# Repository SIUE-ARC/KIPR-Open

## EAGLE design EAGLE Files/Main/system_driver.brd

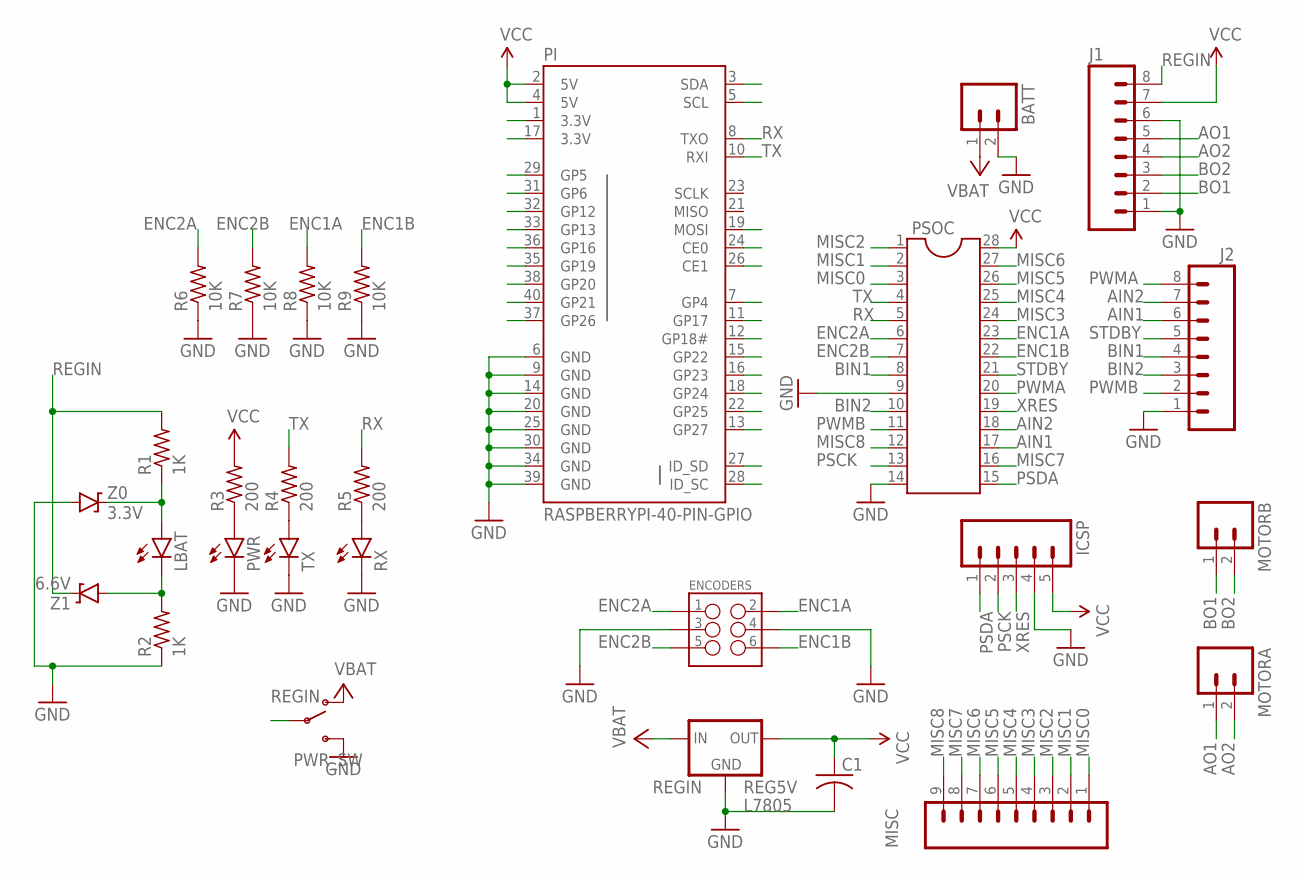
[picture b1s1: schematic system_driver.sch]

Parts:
BATT: M023.5MM; SCREWTERMINAL-3.5MM-2
C1: C-US025-024X044; C025-024X044
ENCODERS: M03X2FEMALE; 2X3
ICSP: M05LOCK_LONGPADS; 1X05_LOCK_LONGPADS
J1, J2: M08LONGPADS; 1X08_LONGPADS
LBAT: LED-FKIT-1206; FKIT-LED-1206
MISC: M09LONGPADS; 1X09_LONGPADS
MOTORA: M023.5MM; SCREWTERMINAL-3.5MM-2
MOTORB: M023.5MM; SCREWTERMINAL-3.5MM-2
PI: RASPBERRYPI-40-PIN-GPIO; 2X20-SHROUDED
PSOC: DIL28-3
PWR: LED-FKIT-1206; FKIT-LED-1206
PWR_SW: SWITCH-SPDTPTH; SWITCH-SPDT
R1, R2: 1K; M1206
R3, R4, R5: 200; M1206
R6, R7, R8, R9: 10K; M1206
REG5V: L7805; 78XXL
RX: LED-FKIT-1206; FKIT-LED-1206
TX: LED-FKIT-1206; FKIT-LED-1206
Z0: 3.3V; SOD-123
Z1: 6.6V; SOD-123

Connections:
3.3V: PI.1 (3.3V), PI.17 (3.3V)
AIN1: J2.6, PSOC.17
AIN2: J2.7, PSOC.18
AO1: J1.5, MOTORA.1
AO2: J1.4, MOTORA.2
BIN1: J2.4, PSOC.8
BIN2: J2.3, PSOC.10
BO1: J1.2, MOTORB.1
BO2: J1.3, MOTORB.2
CE0: PI.24 (CE0)
CE1: PI.26 (CE1)
ENC1A: ENCODERS.2, PSOC.23, R8.2
ENC1B: ENCODERS.6, PSOC.22, R9.2
ENC2A: ENCODERS.1, PSOC.6, R6.2
ENC2B: ENCODERS.5, PSOC.7, R7.2
GND: BATT.2, C1.2, ENCODERS.3, ENCODERS.4, ICSP.4, J1.1, J1.6, J2.1, PI.6 (GND), PI.9 (GND), PI.14 (GND), PI.20 (GND), PI.25 (GND), PI.30 (GND), PI.34 (GND), PI.39 (GND), PSOC.9, PSOC.14, PWR.C, PWR_SW.3 (S), R2.1, R6.1, R7.1, R8.1, R9.1, REG5V.IN (GND), RX.C, TX.C, Z0.A
GP4: PI.7 (GP4)
GP5: PI.29 (GP5)
GP6: PI.31 (GP6)
GP12: PI.32 (GP12)
GP13: PI.33 (GP13)
GP16: PI.36 (GP16)
GP17: PI.11 (GP17)
GP18: PI.12 (GP18#)
GP19: PI.35 (GP19)
GP20: PI.38 (GP20)
GP21: PI.40 (GP21)
GP22: PI.15 (GP22)
GP23: PI.16 (GP23)
GP24: PI.18 (GP24)
GP25: PI.22 (GP25)
GP26: PI.37 (GP26)
GP27: PI.13 (GP27)
ID_SC: PI.28 (ID_SC)
ID_SD: PI.27 (ID_SD)
MISC0: MISC.1, PSOC.3
MISC1: MISC.2, PSOC.2
MISC2: MISC.3, PSOC.1
MISC3: MISC.4, PSOC.24
MISC4: MISC.5, PSOC.25
MISC5: MISC.6, PSOC.26
MISC6: MISC.7, PSOC.27
MISC7: MISC.8, PSOC.16
MISC8: MISC.9, PSOC.12
MOSI: PI.19 (MOSI)
unnamed: LBAT.A, R1.1, Z0.C
unnamed: LBAT.C, R2.2, Z1.A
unnamed: PWR.A, R3.1
unnamed: R4.1, TX.A
unnamed: R5.1, RX.A
PI_SCL: PI.5 (SCL)
PI_SDA: PI.3 (SDA)
PSCK: ICSP.2, PSOC.13
PSDA: ICSP.1, PSOC.15
PWMA: J2.8, PSOC.20
PWMB: J2.2, PSOC.11
REGIN: J1.8, PWR_SW.2, R1.2, REG5V.OUT (IN), Z1.C
RX: PI.8 (TXO), PSOC.5, R5.2
STDBY: J2.5, PSOC.21
TX: PI.10 (RXI), PSOC.4, R4.2
V+: BATT.1, PWR_SW.1 (O)
VCC: C1.1, ICSP.5, J1.7, PI.2 (5V), PI.4 (5V), PSOC.28, R3.2, REG5V.GND (OUT)
XRES: ICSP.3, PSOC.19

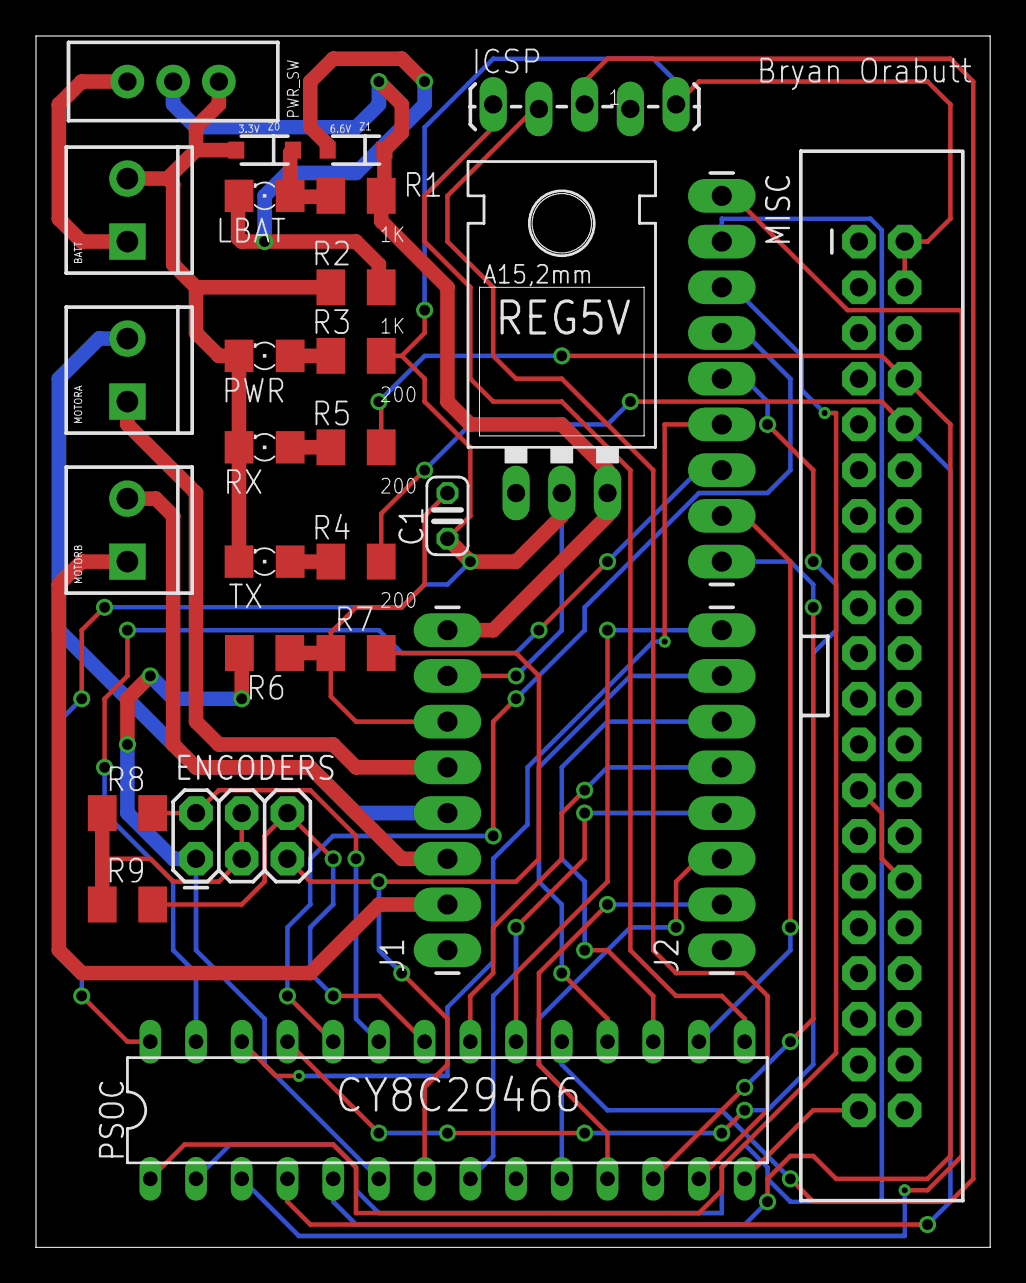
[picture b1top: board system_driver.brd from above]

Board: 2 copper layers, 53.0 x 67.3 mm, 28 parts (0 on the bottom side), 39 nets.

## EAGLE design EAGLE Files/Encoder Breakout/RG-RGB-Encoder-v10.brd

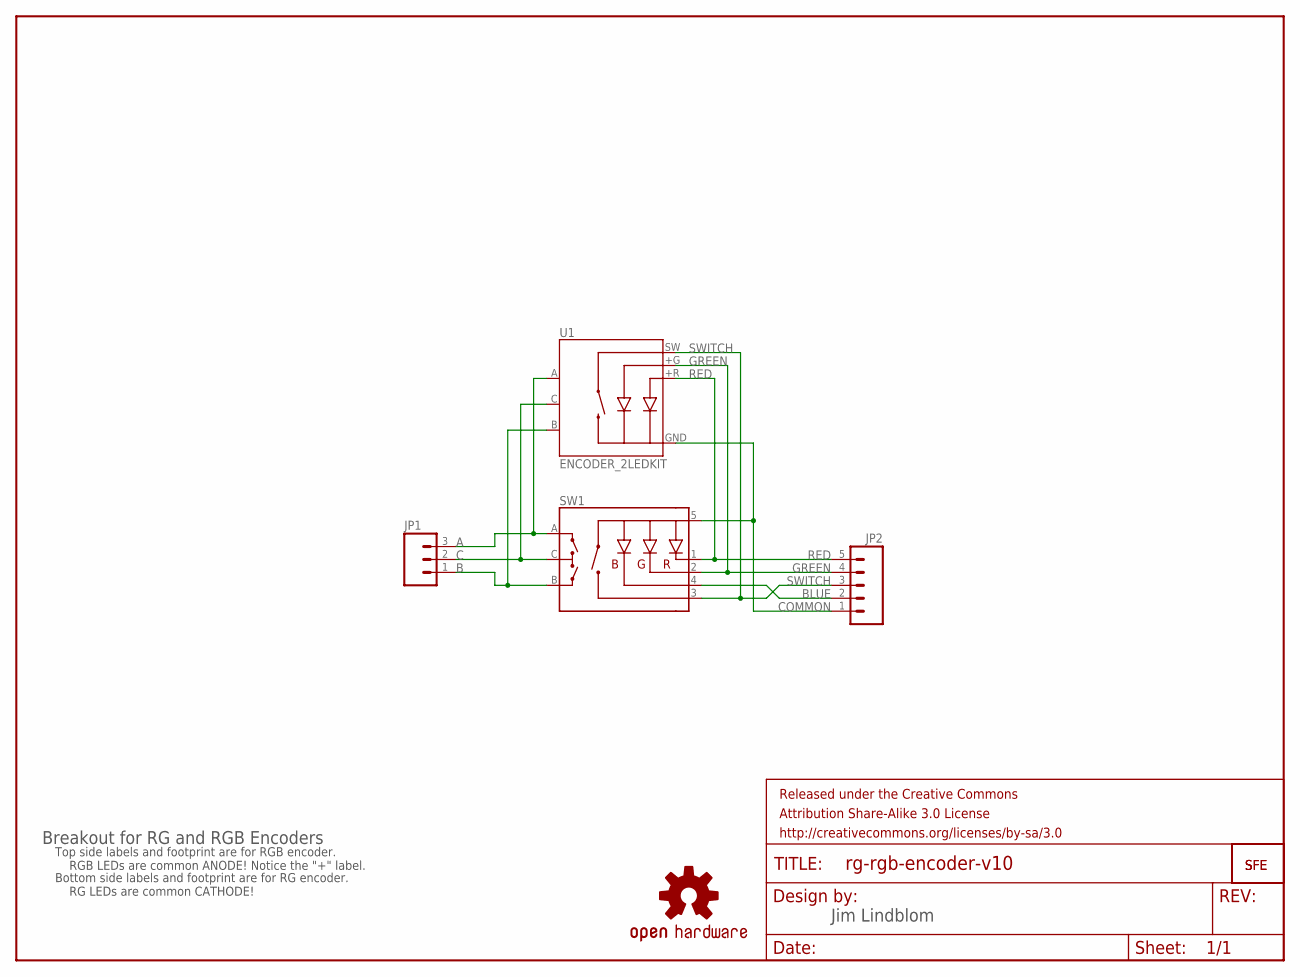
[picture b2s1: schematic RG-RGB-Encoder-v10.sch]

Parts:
FRAME1: FRAME-LETTER; CREATIVE_COMMONS
JP1: M03PTH; 1X03
JP2: M05PTH; 1X05
JP3, JP4: LOGO-SFESK; SFE-LOGO-FLAME
SW1: ENCODER_RGB_CAKIT; ENCODER_LED_3_KIT
U1: ENCODER_2LEDKIT; ENCODER_LED_2_KIT
U$2: OSHW-LOGOS; OSHW-LOGO-S

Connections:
A: JP1.3, SW1.A, U1.A
B: JP1.1, SW1.B, U1.B
BLUE: JP2.2, SW1.4 (-B)
C: JP1.2, SW1.C, U1.C
COMMON: JP2.1, SW1.5 (+), U1.GND (-)
GREEN: JP2.4, SW1.2 (-G), U1.+G
RED: JP2.5, SW1.1 (-R), U1.+R
SWITCH: JP2.3, SW1.3 (SW), U1.SW

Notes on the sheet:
Jim Lindblom
Breakout for RG and RGB Encoders
Top side labels and footprint are for RGB encoder. RGB LEDs are common ANODE! Notice the "+" label.
Bottom side labels and footprint are for RG encoder. RG LEDs are common CATHODE!

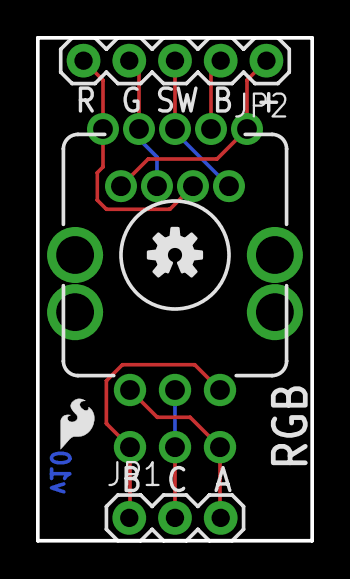
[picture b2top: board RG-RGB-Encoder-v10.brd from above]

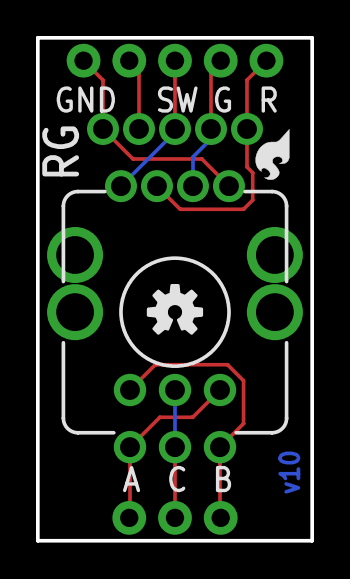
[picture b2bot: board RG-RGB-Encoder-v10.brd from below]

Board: 2 copper layers, 15.2 x 27.9 mm, 9 parts (3 on the bottom side), 8 nets.

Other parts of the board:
U$1: OSHW-LOGOS; OSHW-LOGO-S

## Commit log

2016-03-03 Added Line Following
2016-03-03 Documentation of the Line Following Program
2016-03-03 Added Documentation from KIPR Website
2016-03-04 Added PCB files for robot 2
    Is it bad that I only hand routed major signals :P?
2016-03-04 Removed output files
2016-03-04 updated EAGLE files
2016-03-24 Robot*
2016-04-01 Updated PCB files, added PSoC code
    Up to date PCB and schematic files for Robot 2's driver control board.
    Also added the PSoC code files and project.
2016-04-01 Fixed code formatting.
2016-04-05 Updated PSoC code
    created PSoC code skeleton
2016-04-05 fixed merge issues?
2016-04-05 test
2016-04-05 Revert "test"
    This reverts commit dc12ec36bb4dee52f280ca925d3d81fe9446090e.
2016-04-05 Fixed PSoC code conflicts and reorganized code in repo
2016-04-07 Added ROS packages
2016-04-07 added skeleton program
    ksjfdlsdjfk
2016-04-07 added .gitignore
2016-04-07 proper baud rate
2016-04-08 psoc no worky :(
    UART literally does nothing :(
2016-04-12 Added Ros-Overview files
2016-04-12 Topics added to ROS-Overview
2016-04-12 Added serial-commands.txt
2016-04-12 psoc command structure works
2016-04-12 Continued working.
2016-04-14 updated control driver. All that is left is velocity calculation.
2016-04-14 reorganized repo folders
2016-04-20 Revised KIPR Board
2016-04-26 Added python serial communication test files
2016-04-26 Added ros uml
2016-04-27 Modified ROS UML
2016-05-06 A few more testing functions for robot2
2016-05-17 Testing folder
2016-05-17 docs
2016-05-21 Velocity calculations fixed.
    TODO:
    Move at velocity
    Look into Servo issues
2016-05-21 Velocity calculations in rev/sec finished.
2016-05-22 Added Bill of Materials for PCB
2016-05-24 Added robot 2 documentation
2016-05-25 Added script to create virtual serial connections
2016-05-25 Proper testing in Virtual Serial Connection Script
2016-06-10 Updated .gitignore
2016-06-11 Began work on light sensor code for starting the robot.
2016-06-11 Updated PSoC chip editor to add PGA and DelSig ADC. Decreased VelTimer by 8 bits to free up a digial block.
2016-06-11 Updated .gitignore to untrack output directories.
2016-06-11 removed redundant files.
2016-06-11 More clutter removed.
2016-06-11 Removed old project (isnt that what git is for :P?)
2016-06-12 Updated documentation.
2016-06-12 Added parts purchased
2016-06-18 Modified debug mode to be software enabled, not hardware.
2016-06-18 Possible dumb fix that shouldnt work.
2016-06-18 Fixed TX routing issue.
2016-06-19 Removed old outdated code (commented blocks)
2016-06-19 Changed servo code.
2016-06-24 Cleaned up comments.
2016-06-25 Added Motor Controller.py
2016-06-25 added motorControl.py
2016-06-25 Added servoControl.py
2016-06-25 Added debug statements to servo and motor control
2016-06-25 Found bug with AIN1/2
2016-06-25 fixed AIN/BIN issue
2016-06-26 Added testing function and set wait time between serial commands to .05 SEC
2016-06-26 Header comments for testing.py
2016-06-26 Added light sensor code.
2016-06-26 removed stupid MS Word backup file and added it to the ignore
2016-06-28 Fixed syntax of motorControl
2016-06-28 Changed terminator_character value
2016-06-28 Another attempt at sending terminator character.
2016-06-28 Spelling mistake.
2016-06-29 Bumped last update
2016-06-29 Stop command fixed.
2016-06-29 Updated encoder code.
2016-06-30 added sensorControl.py
2016-06-30 adding PID to motorControl
2016-06-30 Added individual drive commands for each motor
2016-06-30 Modified motorControl to use PID control
2016-07-01 Added Command, Drive, and Turn
2016-07-01 ADCs changed to SAR6, added timer for ultrasonic
2016-07-01 Added more command stuff
2016-07-01 Added drive and turn to Command
2016-07-01 Added Raspi LED pin
2016-07-02 Started writing new code for reflect sensors and ultrasonic
2016-07-02 Modified testing for hardware
2016-07-02 get response now returns the direct values
2016-07-02 Tweaks for PID speed control
2016-07-02 Fixed encoder drive command
2016-07-02 Tweaked encoder turn command
2016-07-02 Deprecated some functions in
2016-07-02 Tweaked
2016-07-02 Renamed and refactored things
2016-07-02 Added 'factory' methods to make building command list easier
2016-07-02 modified comment blocks
2016-07-02 Ultrasound code added. Light Sensor code reworked.
2016-07-02 added ultrasound command.
2016-07-02 stupid ass .pep file doesnt update til i close PSoC designer.
2016-07-03 Fixed PSOC code not compiling and added more debug statements for encoders
2016-07-03 Cleaned up debug statements in encoders
2016-07-03 Encoder ISR updated
2016-07-03 Even more elaborate ISR
2016-07-03 pep file
2016-07-03 Interrupt masks updated.
2016-07-03 Updated ultrasound ISR
2016-07-03 changed debug default state
2016-07-03 encoder attempt 4
2016-07-03 encoders with double precision
2016-07-03 Encoder tweaks
2016-07-03 Added ack to psoc
2016-07-03 Added startup service
2016-07-04 Added BucketCommands, Raspi, and Raspicommands
2016-07-04 Fixed last update
2016-07-04 Fixed elif
2016-07-04 Fixed range
2016-07-04 Fixed debug
2016-07-04 Fixed pin range
2016-07-04 Fixed range and set proper board mode
2016-07-04 Added cleanup
2016-07-04 All serial communication expects a response and can throw an exception
2016-07-04 Updated last_update tag
2016-07-04 Fixed compile and link errors
2016-07-04 failed in Command is command
2016-07-04 Double check that pin 02 is connected to the ultrasonic timer
2016-07-05 Basic Command Framework is complete
2016-07-05 Fixed python syntax
2016-07-05 Updated game rules pdf
2016-07-05 robot.py cleanup
2016-07-05 Added command to square up to pipe
2016-07-05 Added backups to gitignore
2016-07-05 Minor corrections
2016-07-05 Ultrasonic tweaks
2016-07-05 Reverted PSoC stuff
2016-07-05 Revert "Minor corrections"
    This reverts commit 572e8203edf4ed91551ff9cfed5b12eb465b64cc.
2016-07-05 Revert "Ultrasonic tweaks"
    This reverts commit 8eb5b6e500ce3cfdfcb181f73c21b4e048f97d15.
2016-07-05 Stupid work around for .asm error
2016-07-05 Fixed Ryan's changes breaking my timer >:(
2016-07-06 Changed order of enable/disable of ultrasonic interrupt.
2016-07-06 Added motor speedup to testing
2016-07-06 Fixed motor control indent
2016-07-06 Fixed tabs
2016-07-06 Fixed indents
2016-07-06 Fixed return value
2016-07-06 attempt to fix ultrasound
2016-07-06 possible ultrasonic fix
2016-07-06 Added keyboard interrupt
2016-07-06 Working on serialCom get response
2016-07-06 Fixed spelling
2016-07-06 Attempted to fix serial com ack
2016-07-06 Added pins for front/rear bumpers
2016-07-06 Fixed command import
2016-07-06 Fixed file naming
2016-07-06 Fixed port
2016-07-06 Fixed private variable
2016-07-06 fixed naming
2016-07-07 Modified all commands to send ACK
2017-05-24 Datasheet for board

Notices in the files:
parts and their libraries:
SparkFun-Electromechanical: Licensing: CC v3.0 Share-Alike You are welcome to use this library for commercial purposes.
SparkFun-Aesthetics: Released under the Creative Commons Attribution Share-Alike 3.0 License
SparkFun-Aesthetics: http://creativecommons.org/licenses/by-sa/3.0
